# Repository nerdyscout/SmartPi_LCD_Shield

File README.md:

# SmartPi_LCD_Shield

Arduino LCD Shield fitting in top half of [DIN Rail Housing of CAMDENBOSS](https://www.camdenboss.com/camden-boss/cbrpi-dr-2-3-clr-pi-b%2c-p2%2c-p3-din-rail-enclosure/c-23/p-23019). A further adapter PCB is needed to connect to the RaspberryPi, see [SmartPi_IO_HAT](https://github.com/nerdyscout/SmartPi_IO_HAT).

But ofcourse this could be used directly with an Arduino as well.

Differnt assembly variants are available:
- LCDisplay and buttons via I2C port expander 
- LCDisplay via 4bit mode (only possible if RTC and RFM are not used!) and buttons on A1 
- RGB backlight of LCD supported 
- optional RTC with measurment of battery voltage at A0
- optional LORA RFM95 modul
- optional SDCard slot for data logging  
- optional buzzer (only via port expander)

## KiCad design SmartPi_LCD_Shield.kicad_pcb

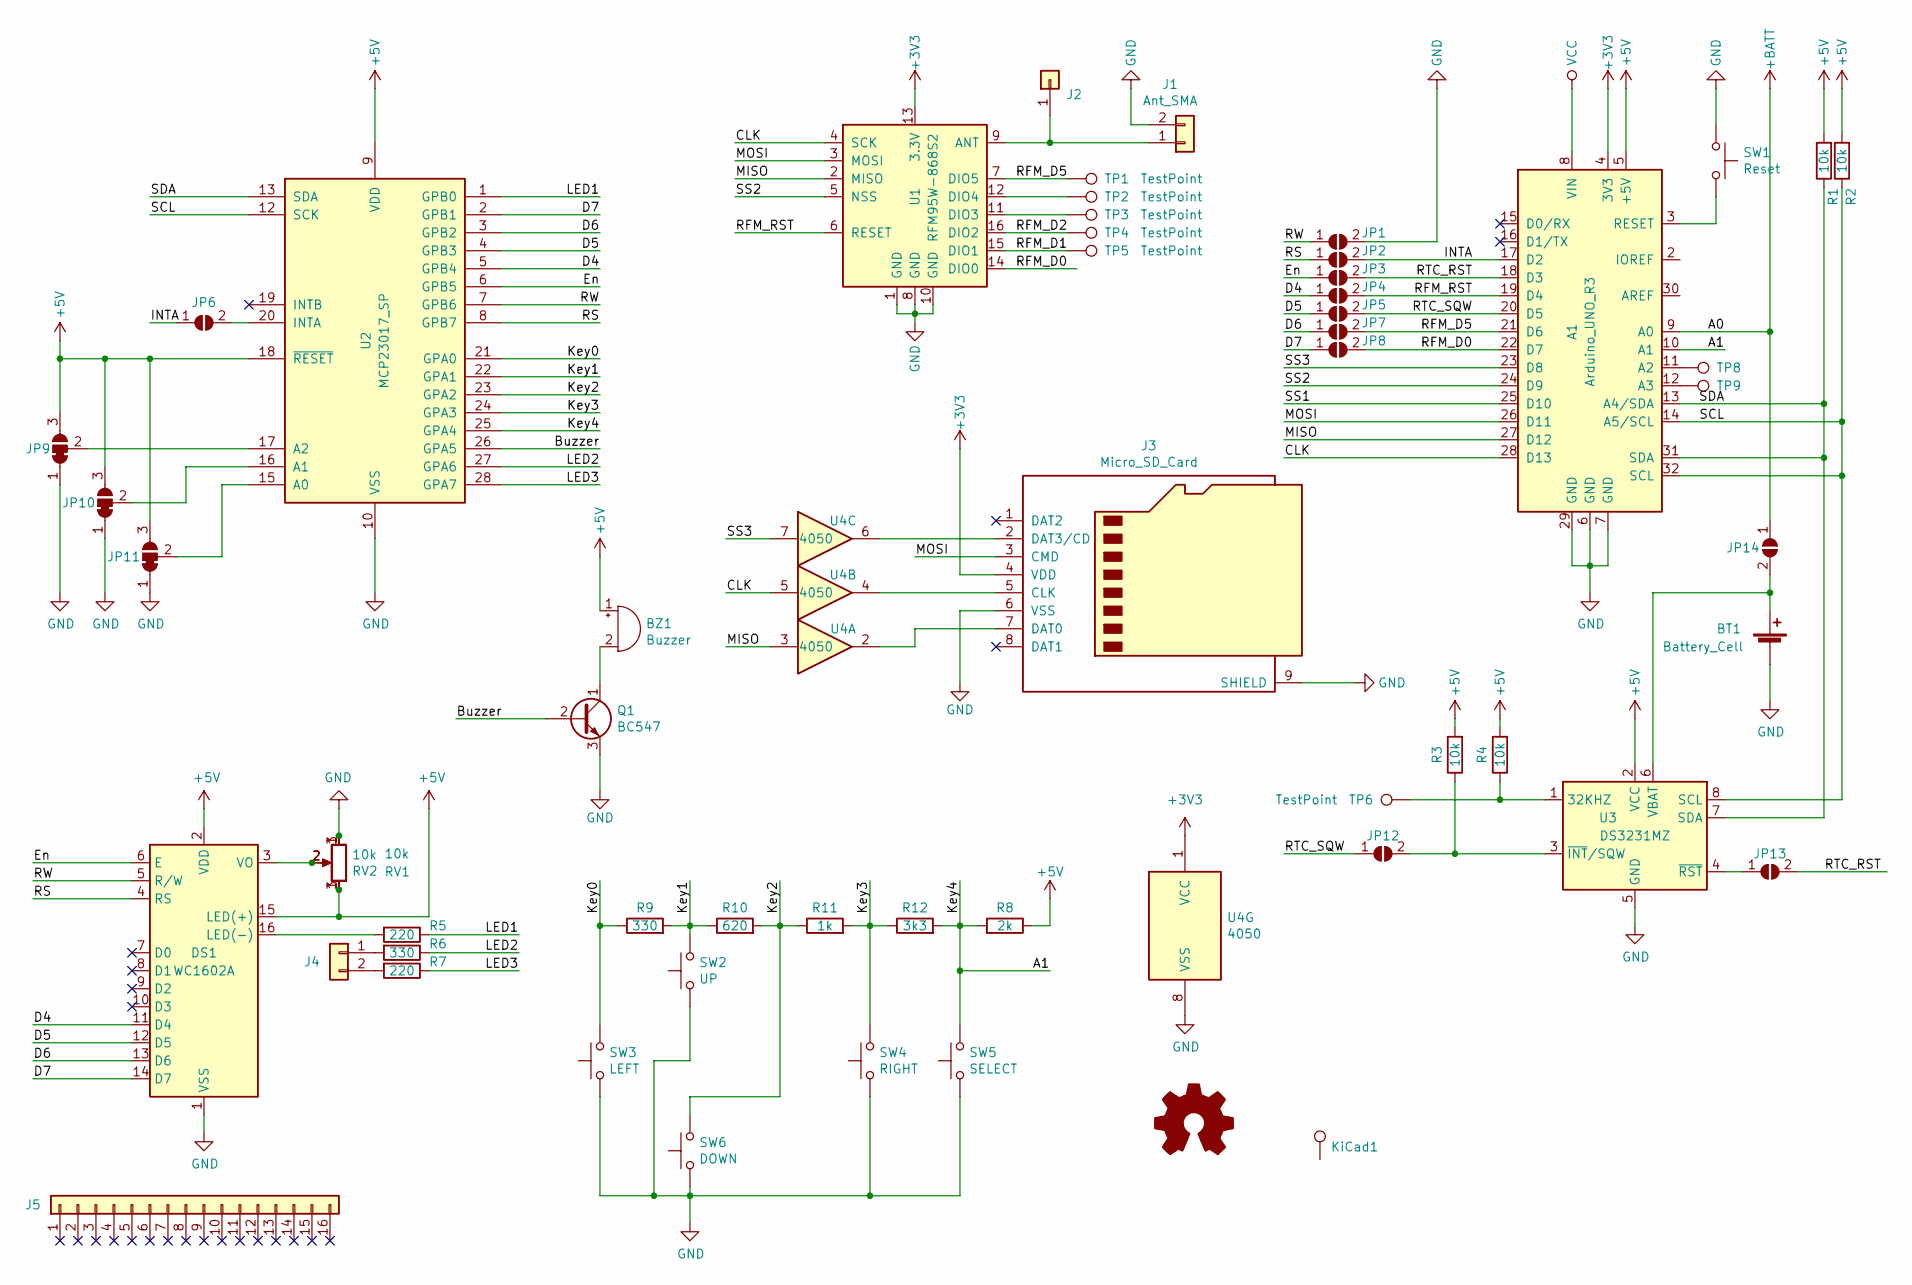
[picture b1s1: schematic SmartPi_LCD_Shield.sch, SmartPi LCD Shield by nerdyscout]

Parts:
A1: Arduino_UNO_R3
BT1: Battery_Cell; BatteryHolder_Keystone_3000_1x12mm
BZ1: Buzzer; MagneticBuzzer_Kingstate_KCG0601
DS1: WC1602A
J1: Ant_SMA; SMA_Amphenol_132289_EdgeMount
J2: Conn_01x01; PinSocket_1x01_P2.54mm_Vertical
J3: Micro_SD_Card; microSD_HC_Wuerth_693072010801
J4: Conn_01x02; PinHeader_1x02_P2.54mm_Vertical
J5: Conn_01x16; PinSocket_1x16_P2.54mm_Vertical
JP1, JP2, JP3, JP4, JP5, JP6, JP7, JP8, JP12, JP13, JP14: SolderJumper_2_Open; SolderJumper-2_P1.3mm_Open_RoundedPad1.0x1.5mm
JP9, JP10, JP11: SolderJumper_3_Bridged12; SolderJumper-3_P1.3mm_Bridged12_RoundedPad1.0x1.5mm_NumberL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
KiCad1: License; KiCad-Logo2_8mm_SilkScreen
LOGO1: Logo_Open_Hardware_Small; OSHW-Logo2_14.6x12mm_SilkScreen
Q1: BC547; TO-92_Inline
R1, R2, R3, R4: 10k; R_Axial_DIN0204_L3.6mm_D1.6mm_P7.62mm_Horizontal
R5, R7: 220; R_Axial_DIN0204_L3.6mm_D1.6mm_P7.62mm_Horizontal
R6, R9: 330; R_Axial_DIN0204_L3.6mm_D1.6mm_P7.62mm_Horizontal
R8: 2k; R_Axial_DIN0204_L3.6mm_D1.6mm_P7.62mm_Horizontal
R10: 620; R_Axial_DIN0204_L3.6mm_D1.6mm_P7.62mm_Horizontal
R11: 1k; R_Axial_DIN0204_L3.6mm_D1.6mm_P7.62mm_Horizontal
R12: 3k3; R_Axial_DIN0204_L3.6mm_D1.6mm_P7.62mm_Horizontal
RV1: 10k; Potentiometer_Bourns_3266P_Horizontal
RV2: 10k; Potentiometer_Bourns_3296X_Horizontal
SW1: Reset; SW_PUSH_6mm
SW2: UP; SW_PUSH_6mm
SW3: LEFT; SW_PUSH_6mm
SW4: RIGHT; SW_PUSH_6mm
SW5: SELECT; SW_PUSH_6mm
SW6: DOWN; SW_PUSH_6mm
TP1, TP2, TP3, TP4, TP5, TP6, TP8, TP9: TestPoint; TestPoint_Pad_D2.0mm
U1: RFM95W-868S2; HOPERF_RFM9XW_SMD
U2: MCP23017_SP; DIP-28_W7.62mm
U3: DS3231MZ; SOIC-8_3.9x4.9mm_P1.27mm
U4: 4050; SOIC-16_3.9x9.9mm_P1.27mm

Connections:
+3V3: A1.4 (3V3), J3.4 (VDD), U1.13 (3.3V), U4.1 (VCC)
+5V: A1.5 (+5V), BZ1.1 (-), DS1.2 (VDD), DS1.15 (LED(+)), JP9.3 (B), JP10.3 (B), JP11.3 (B), R1.2, R2.2, R3.2, R4.2, R8.1, RV1.1, RV2.3, U2.9 (VDD), U2.18 (~RESET~), U3.2 (VCC)
+BATT: A1.9 (A0), JP14.1 (A)
/A1: A1.10 (A1), R8.2, R12.2, SW5.2, U2.25 (GPA4)
/Buzzer: Q1.2 (B), U2.26 (GPA5)
/CLK: A1.28 (D13), U1.4 (SCK), U4.5
/D4: DS1.11 (D4), JP4.1 (A), U2.5 (GPB4)
/D5: DS1.12 (D5), JP5.1 (A), U2.4 (GPB3)
/D6: DS1.13 (D6), JP7.1 (A), U2.3 (GPB2)
/D7: DS1.14 (D7), JP8.1 (A), U2.2 (GPB1)
/En: DS1.6 (E), JP3.1 (A), U2.6 (GPB5)
/INTA: A1.17 (D2), JP2.2 (B), JP6.1 (A)
/Key0: R9.1, SW3.2, U2.21 (GPA0)
/Key1: R9.2, R10.1, SW2.2, U2.22 (GPA1)
/Key2: R10.2, R11.1, SW6.2, U2.23 (GPA2)
/Key3: R11.2, R12.1, SW4.2, U2.24 (GPA3)
/LED1: R5.1, U2.1 (GPB0)
/LED2: R6.1, U2.27 (GPA6)
/LED3: R7.1, U2.28 (GPA7)
/MISO: A1.27 (D12), U1.2 (MISO), U4.3
/MOSI: A1.26 (D11), J3.3 (CMD), U1.3 (MOSI)
/RFM_D0: A1.22 (D7), JP8.2 (B), U1.14 (DIO0)
/RFM_D1: TP5.1, U1.15 (DIO1)
/RFM_D2: TP4.1, U1.16 (DIO2)
/RFM_D5: A1.21 (D6), JP7.2 (B), TP1.1, U1.7 (DIO5)
/RFM_RST: A1.19 (D4), JP4.2 (B), U1.6 (RESET)
/RS: DS1.4 (RS), JP2.1 (A), U2.8 (GPB7)
/RTC_RST: A1.18 (D3), JP3.2 (B), JP13.2 (B)
/RTC_SQW: A1.20 (D5), JP5.2 (B), JP12.1 (A)
/RW: DS1.5 (R/W), JP1.1 (A), U2.7 (GPB6)
/SCL: A1.14 (A5/SCL), A1.32 (SCL), R2.1, U2.12 (SCK), U3.8 (SCL)
/SDA: A1.13 (A4/SDA), A1.31 (SDA), R1.1, U2.13 (SDA), U3.7 (SDA)
/SS2: A1.24 (D9), U1.5 (NSS)
/SS3: A1.23 (D8), U4.7
GND: A1.6 (GND), A1.7 (GND), A1.29 (GND), BT1.2 (-), DS1.1 (VSS), J1.2, J3.6 (VSS), J3.9 (SHIELD), JP1.2 (B), JP9.1 (A), JP10.1 (A), JP11.1 (A), Q1.3 (E), RV1.3, RV2.1, SW1.1, SW2.1, SW3.1, SW4.1, SW5.1, SW6.1, U1.1 (GND), U1.8 (GND), U1.10 (GND), U2.10 (VSS), U3.5 (GND), U4.8 (VSS)
unnamed: A1.3 (RESET), SW1.2
unnamed: A1.11 (A2), TP8.1
unnamed: A1.12 (A3), TP9.1
unnamed: BT1.1 (+), JP14.2 (B), U3.6 (VBAT)
unnamed: BZ1.2 (+), Q1.1 (C)
unnamed: DS1.3 (VO), RV1.2, RV2.2
unnamed: DS1.16 (LED(-)), R5.2
unnamed: J1.1, J2.1, U1.9 (ANT)
unnamed: J3.2 (DAT3/CD), U4.6
unnamed: J3.5 (CLK), U4.4
unnamed: J3.7 (DAT0), U4.2
unnamed: J4.1, R6.2
unnamed: J4.2, R7.2
unnamed: JP6.2 (B), U2.20 (INTA)
unnamed: JP9.2 (C), U2.17 (A2)
unnamed: JP10.2 (C), U2.16 (A1)
unnamed: JP11.2 (C), U2.15 (A0)
unnamed: JP12.2 (B), R3.1, U3.3 (~INT~/SQW)
unnamed: JP13.1 (A), U3.4 (~RST)
unnamed: R4.1, TP6.1, U3.1 (32KHZ)
unnamed: TP2.1, U1.12 (DIO4)
unnamed: TP3.1, U1.11 (DIO3)

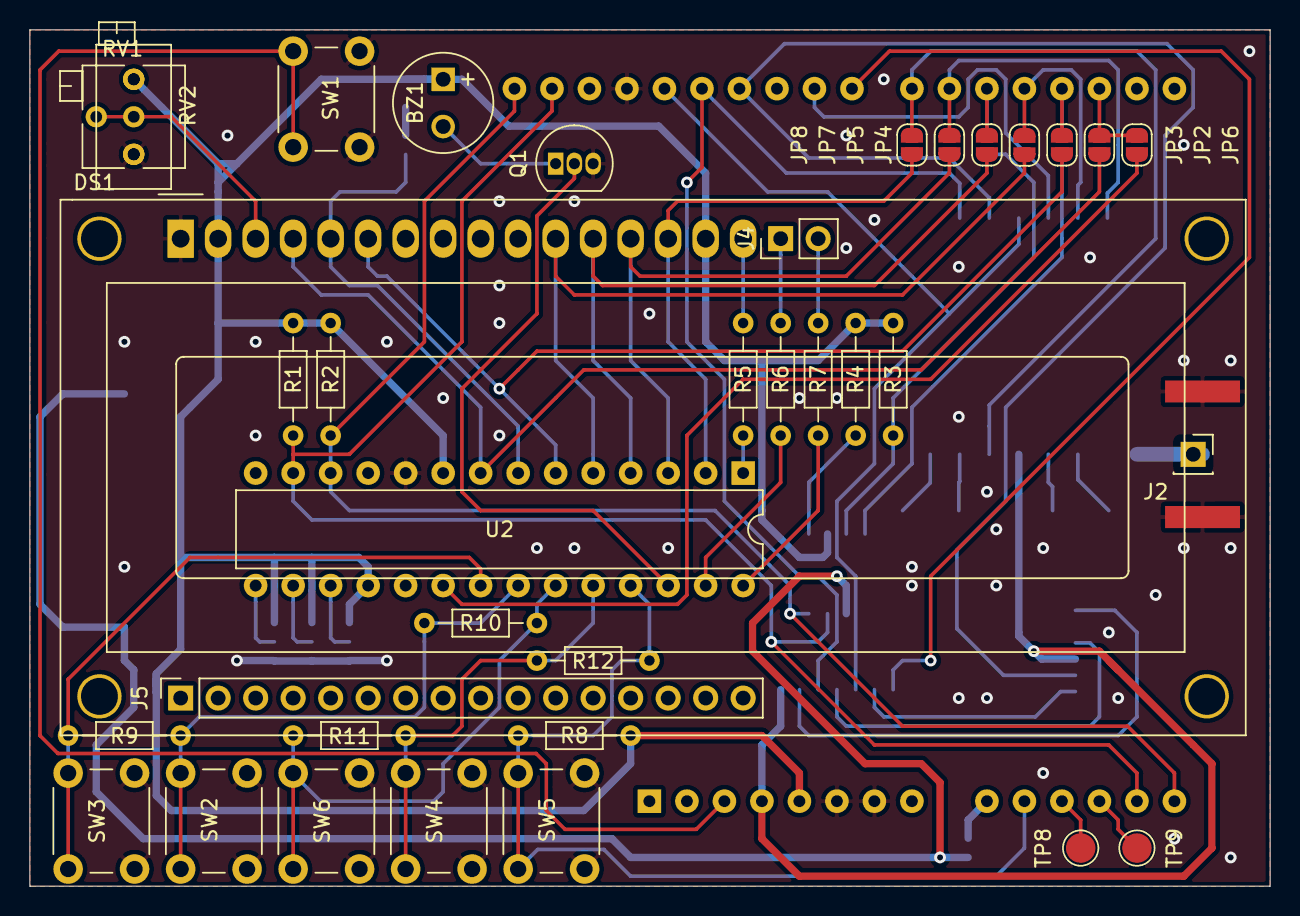
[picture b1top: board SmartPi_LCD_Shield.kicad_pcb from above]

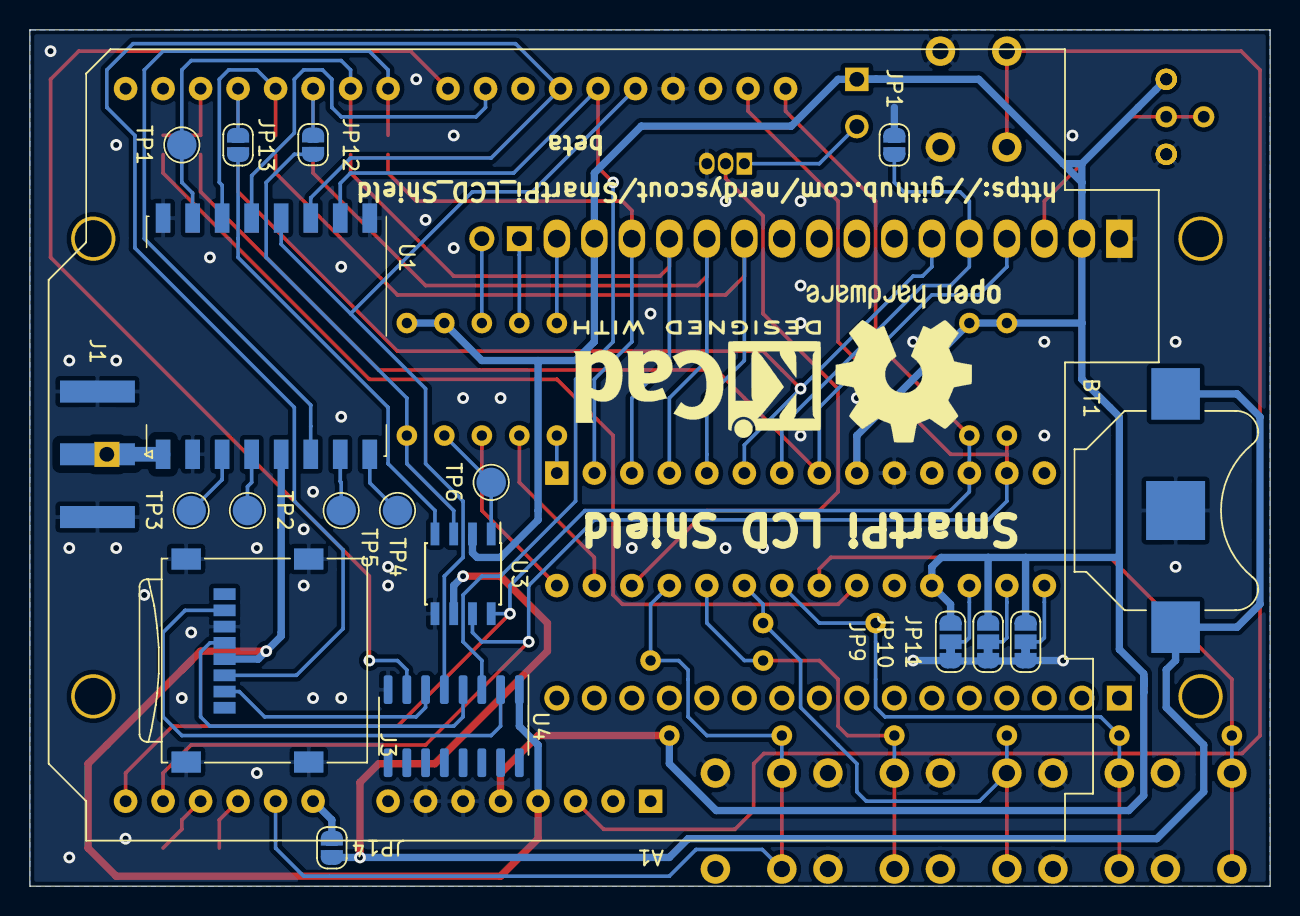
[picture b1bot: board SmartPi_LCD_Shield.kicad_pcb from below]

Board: 2 copper layers, 84.0 x 58.0 mm, 58 parts (22 on the bottom side), 57 nets.

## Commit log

2019-05-15 finished routing
2019-05-21 added hexbuffer for sd card
2019-05-24 routing complete with hex buffer
2019-06-17 added option for analog buttons
2019-06-17 new description
2019-06-17 page title
2019-06-18 Create LICENSE
